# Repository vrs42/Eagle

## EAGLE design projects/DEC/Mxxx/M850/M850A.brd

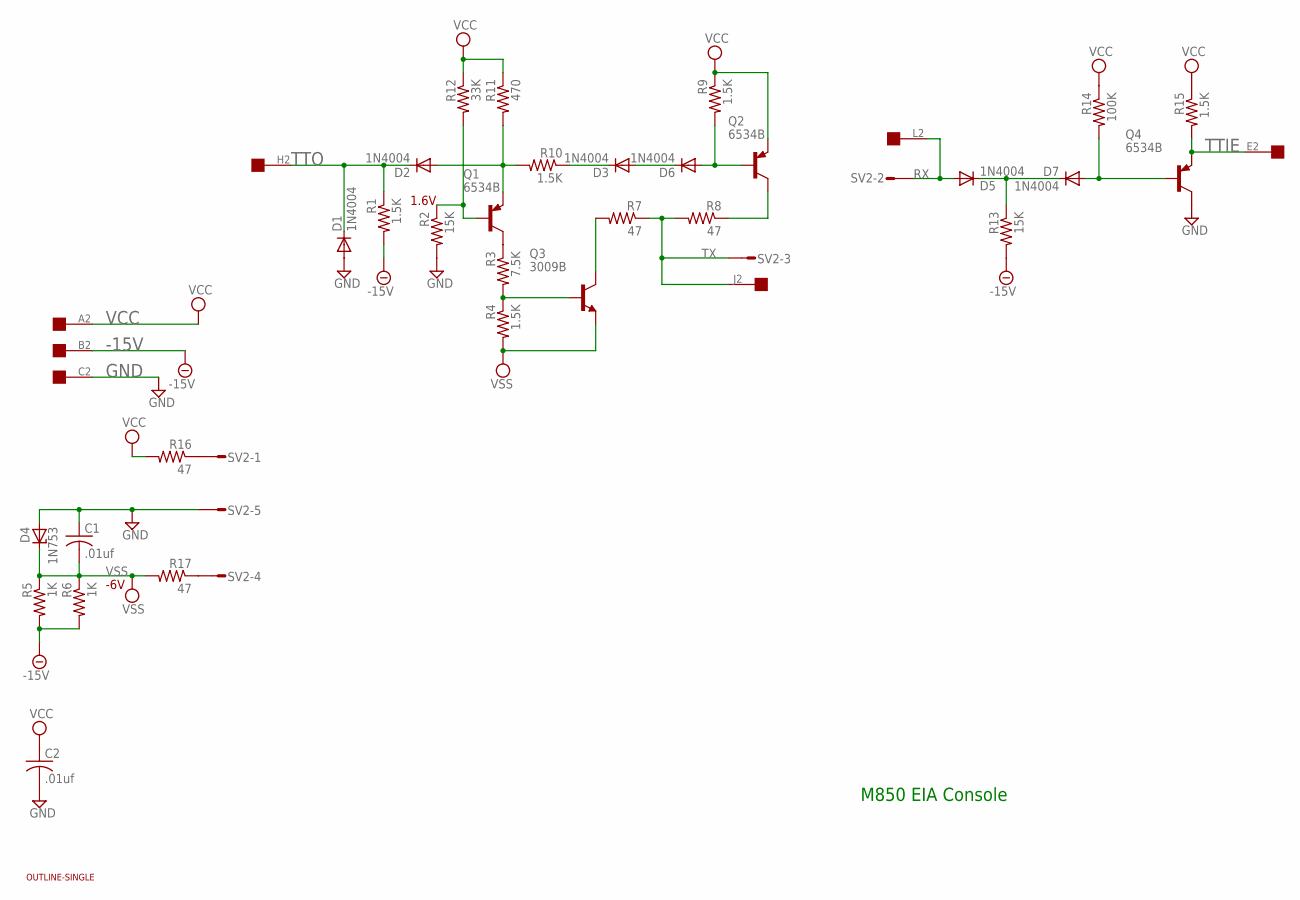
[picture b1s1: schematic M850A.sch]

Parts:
C1, C2: .01uf; C050-025X075
D1, D2, D3, D5, D6, D7: 1N4004; DO35-10
D4: 1N753; DO35Z10
EDGE: EDGE-1; EDGE-CON1
Q1, Q2, Q4: 6534B; TO92/
Q3: 3009B; TO18-
R1, R4, R9, R10, R15: 1.5K; 0207/10
R2, R13: 15K; 0207/10
R3: 7.5K; 0207/10
R5, R6: 1K; 0207/10
R7, R8, R16, R17: 47; 0207/10
R11: 470; 0207/10
R12: 33K; 0207/10
R14: 100K; 0207/10
SV2: L08P
U$1: OUTLINE-SINGLE; SINGLE

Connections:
-15V: EDGE.B2, R1.2, R5.2, R6.2, R13.2
GND: C1.1, C2.2, D1.A, D4.A, EDGE.C2, Q4.3 (C), R2.2, SV2.5
unnamed: Q2.3 (C), R8.1
unnamed: D7.A, Q4.2 (B), R14.2
unnamed: Q1.3 (C), R3.1
unnamed: R17.1, SV2.4
unnamed: Q3.3 (C), R7.2
unnamed: D5.C, D7.C, R13.1
unnamed: D2.A, Q1.1 (E), R10.2, R11.2
unnamed: D6.A, Q2.2 (B), R9.2
unnamed: Q1.2 (B), R2.1, R12.2
unnamed: D3.A, D6.C
unnamed: D3.C, R10.1
unnamed: Q3.2 (B), R3.2, R4.1
unnamed: R16.1, SV2.1
RX: D5.A, EDGE.L2, SV2.2
TTIE: EDGE.E2, Q4.1 (E), R15.2
TTO: D1.C, D2.C, EDGE.H2, R1.1
TX: EDGE.J2, R7.1, R8.2, SV2.3
VCC: C2.1, EDGE.A2, Q2.1 (E), R9.1, R11.1, R12.1, R14.1, R15.1, R16.2
VSS: C1.2, D4.C, Q3.1 (E), R4.2, R5.1, R6.1, R17.2

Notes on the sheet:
M850 EIA Console
1.6V
-6V

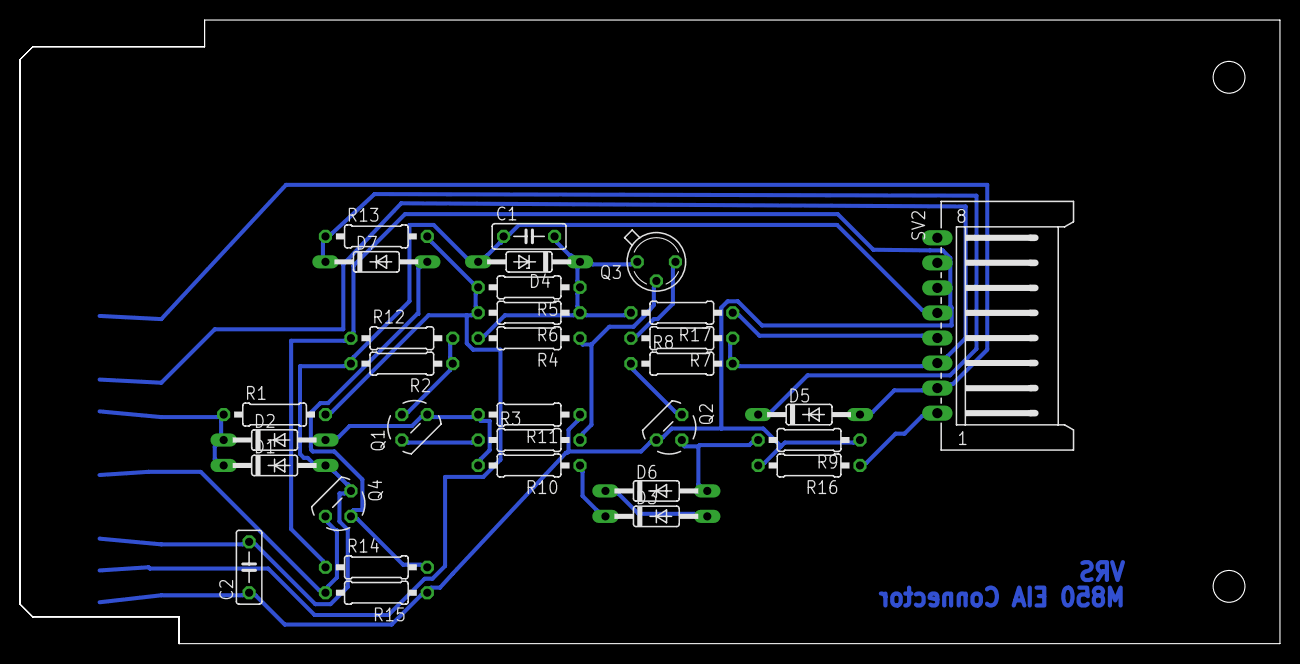
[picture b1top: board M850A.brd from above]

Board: 2 copper layers, 125.7 x 62.2 mm, 33 parts (0 on the bottom side), 21 nets.

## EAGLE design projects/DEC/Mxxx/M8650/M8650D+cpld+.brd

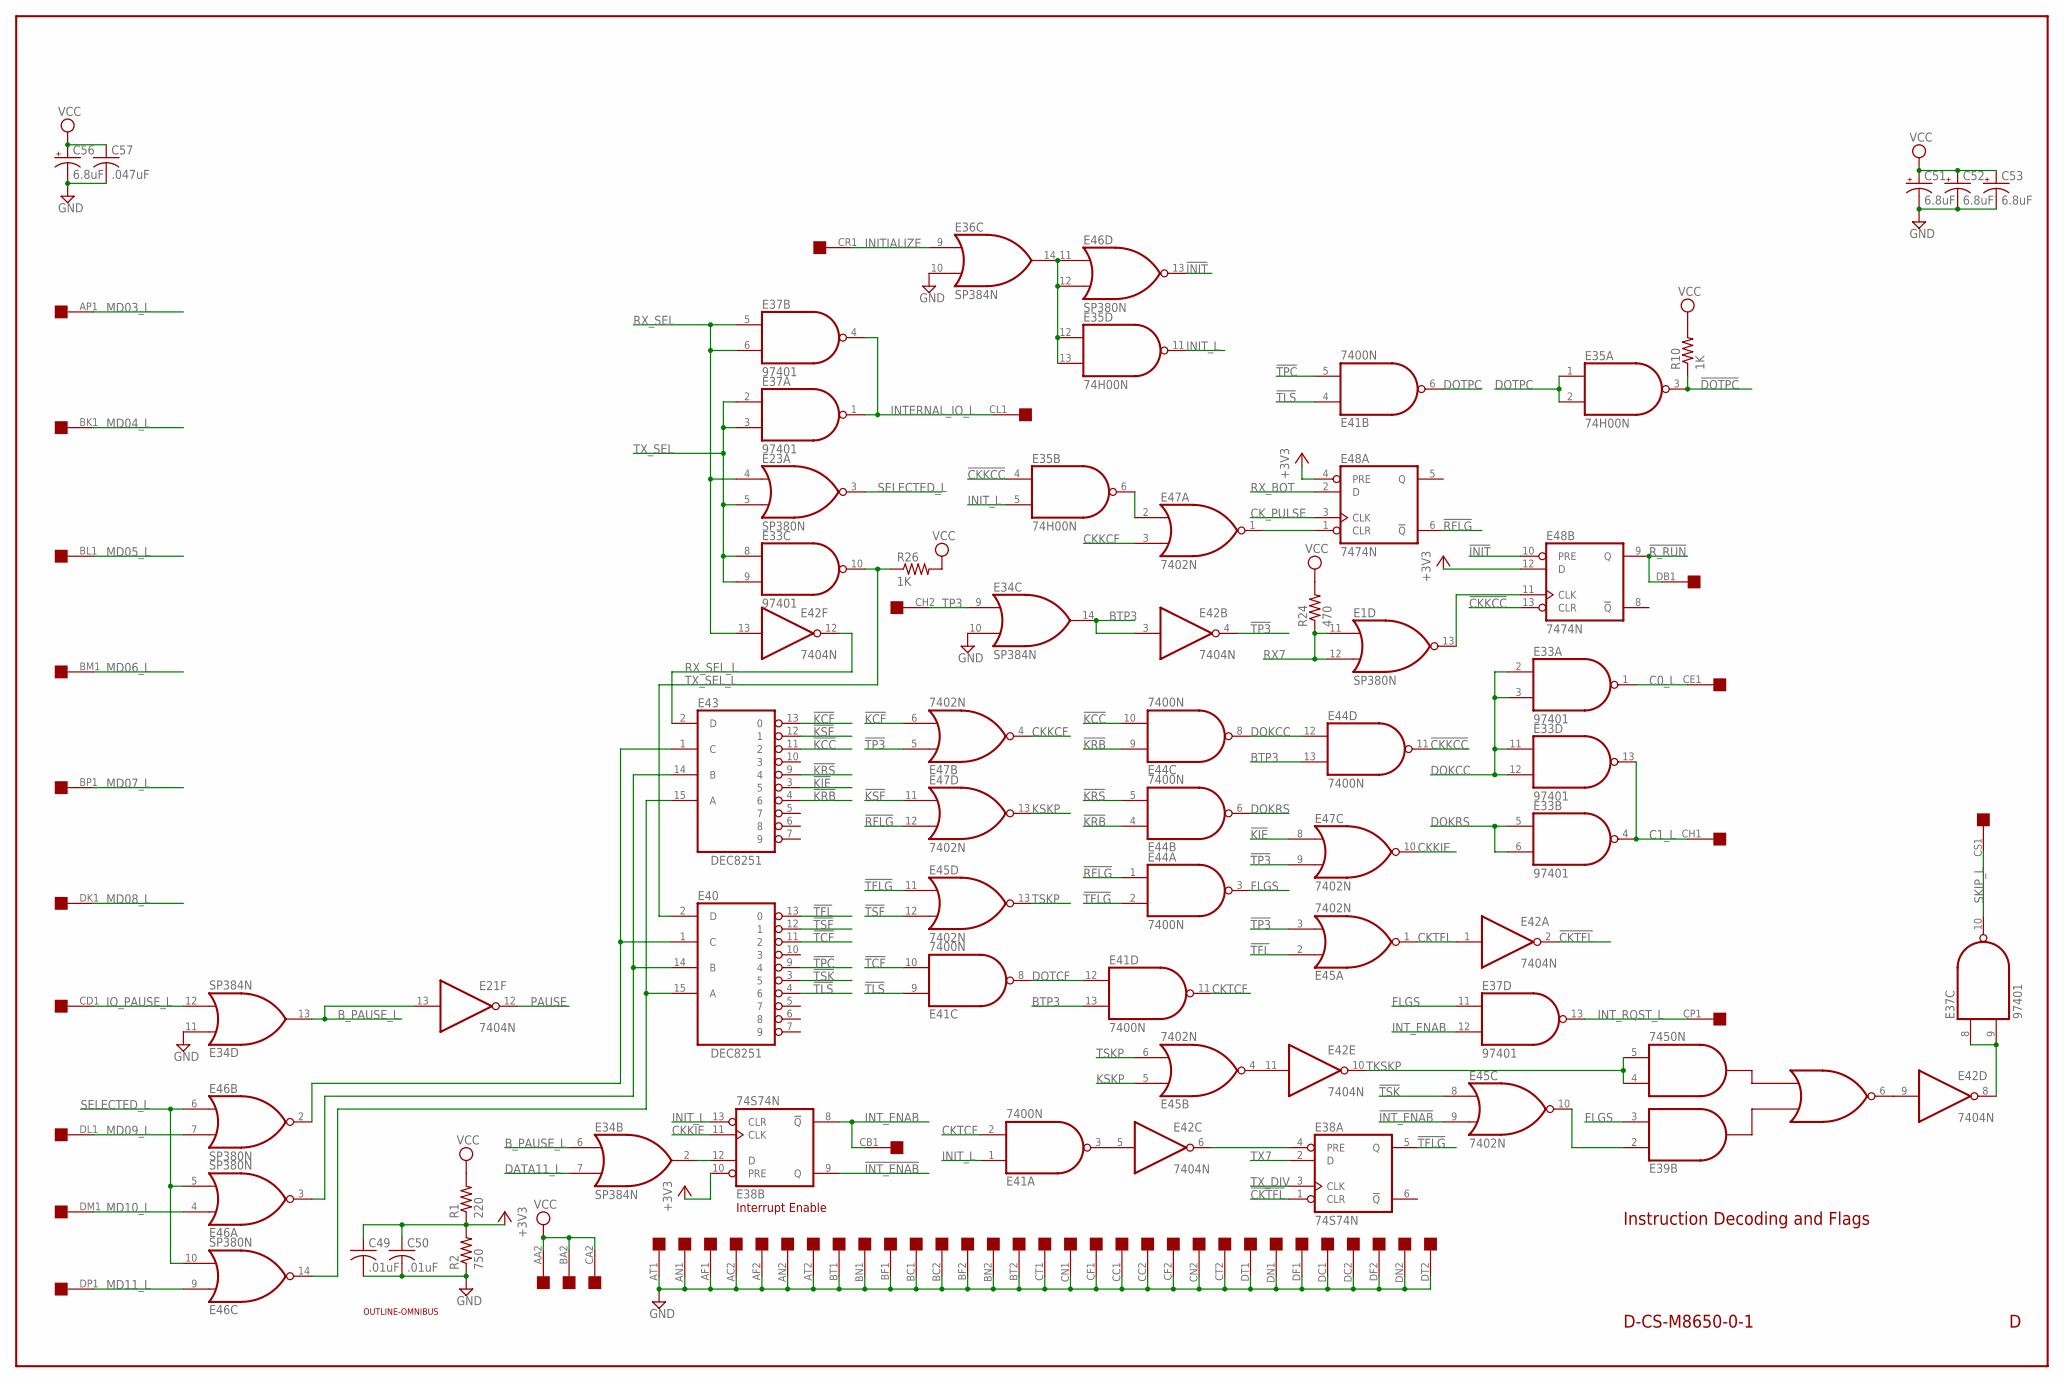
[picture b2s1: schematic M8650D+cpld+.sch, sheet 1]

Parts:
C49, C50: .01uF; C050-025X075
C51, C52, C53, C56: 6.8uF; E12-8
C57: .047uF; C050-025X075
E1, E23, E46: SP380N; DIL14
E21, E42: 7404N; DIL14
E33, E37: 97401; DIL14
E34, E36: SP384N; DIL14
E35: 74H00N; DIL14
E38: 74S74N; DIL14
E39: 7450N; DIL14
E40, E43: DEC8251; DIL16
E41, E44: 7400N; DIL14
E45, E47: 7402N; DIL14
E48: 7474N; DIL14
R1: 220; 0207/10
R2: 750; 0207/10
R10, R26: 1K; 0207/10
R24: 470; 0207/10
U$1: OUTLINE-OMNIBUS; OMNIBUS
U$2: OMNIBUS; EDGE-CON8

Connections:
!CKKCC: E35.4 (I0), E44.11 (O), E48.13 (CLR)
!CKTFL: E38.1 (CLR), E42.2 (O)
!DOTPC: E35.3 (O), R10.1; also elsewhere on the board
!INIT: E46.13 (O), E48.10 (PRE); also elsewhere on the board
!INT_ENAB: E38.9 (Q), E45.9 (I1)
!KCC: E43.11 (2), E44.10 (I1)
!KCF: E43.13 (0), E47.6 (I1)
!KIE: E43.3 (5), E47.8 (I0)
!KRB: E43.4 (6), E44.4 (I0), E44.9 (I0)
!KRS: E43.9 (4), E44.5 (I1)
!KSF: E43.12 (1), E47.11 (I0)
!RFLG: E44.1 (I0), E47.12 (I1), E48.6 (!Q)
!R_RUN: E48.9 (Q), U$2.DB1
!TCF: E40.11 (2), E41.10 (I1)
!TFL: E40.13 (0), E45.2 (I0)
!TFLG: E38.5 (Q), E44.2 (I1), E45.11 (I0)
!TLS: E40.4 (6), E41.4 (I0), E41.9 (I0)
!TP3: E42.4 (O), E45.3 (I1), E47.5 (I0), E47.9 (I1)
!TPC: E40.9 (4), E41.5 (I1)
!TSF: E40.12 (1), E45.12 (I1)
!TSK: E40.3 (5), E45.8 (I0)
+3V3: C49.1, C50.1, E38.10 (PRE), E48.4 (PRE), E48.12 (D), R1.1, R2.2; also elsewhere on the board
BTP3: E34.14 (O), E41.13 (I1), E42.3 (I), E44.13 (I1); also elsewhere on the board
B_PAUSE_L: E21.13 (I), E34.6 (I0), E34.13 (O)
C0_L: E33.1 (O), U$2.CE1
C1_L: E33.4 (O), E33.13 (O), U$2.CH1
CKKCF: E47.3 (I1), E47.4 (O)
CKKIE: E38.11 (CLK), E47.10 (O)
CKTCF: E41.2 (I1), E41.11 (O)
CKTFL: E42.1 (I), E45.1 (O)
CK_PULSE: E48.3 (CLK); also elsewhere on the board
DATA11_L: E34.7 (I1); also elsewhere on the board
DOKCC: E33.2 (I0), E33.3 (I1), E33.11 (I0), E33.12 (I1), E44.8 (O), E44.12 (I0)
DOKRS: E33.5 (I0), E33.6 (I1), E44.6 (O); also elsewhere on the board
DOTCF: E41.8 (O), E41.12 (I0)
DOTPC: E35.1 (I0), E35.2 (I1), E41.6 (O); also elsewhere on the board
FLGS: E37.11 (I0), E39.3 (I2), E44.3 (O)
GND: C49.2, C50.2, C51.-, C52.-, C53.-, C56.-, C57.2, E1.1 (GND), E21.7 (GND), E23.1 (GND), E33.7 (GND), E34.1 (GND), E34.10 (I1), E34.11 (I0), E35.7 (GND), E36.1 (GND), E36.10 (I1), E37.7 (GND), E38.7 (GND), E39.7 (GND), E40.8 (GND), E41.7 (GND), E42.7 (GND), E43.8 (GND), E44.7 (GND), E45.7 (GND), E46.1 (GND), E47.7 (GND), E48.7 (GND), R2.1, U$2.AC2, U$2.AF1, U$2.AF2, U$2.AN1, U$2.AN2, U$2.AT1, U$2.AT2, U$2.BC1, U$2.BC2, U$2.BF1, U$2.BF2, U$2.BN1, U$2.BN2, U$2.BT1, U$2.BT2, U$2.CC1, U$2.CC2, U$2.CF1, U$2.CF2, U$2.CN1, U$2.CN2, U$2.CT1, U$2.CT2, U$2.DC1, U$2.DC2, U$2.DF1, U$2.DF2, U$2.DN1, U$2.DN2, U$2.DT1, U$2.DT2; also elsewhere on the board
INITIALIZE: E36.9 (I0), U$2.CR1
INIT_L: E35.5 (I1), E35.11 (O), E38.13 (CLR), E41.1 (I0); also elsewhere on the board
INTERNAL_IO_L: E37.1 (O), E37.4 (O), U$2.CL1
INT_ENAB: E37.12 (I1), E38.8 (!Q), U$2.CB1
INT_RQST_L: E37.13 (O), U$2.CP1
IO_PAUSE_L: E34.12 (I1), U$2.CD1
KSKP: E45.5 (I0), E47.13 (O)
MD03_L: U$2.AP1; also elsewhere on the board
MD04_L: U$2.BK1; also elsewhere on the board
MD05_L: U$2.BL1; also elsewhere on the board
MD06_L: U$2.BM1; also elsewhere on the board
MD07_L: U$2.BP1; also elsewhere on the board
MD08_L: U$2.DK1; also elsewhere on the board
MD09_L: E46.7 (I1), U$2.DL1
MD10_L: E46.4 (I0), U$2.DM1
MD11_L: E46.9 (I0), U$2.DP1
unnamed: E34.2 (O), E38.12 (D)
unnamed: E42.11 (I), E45.4 (O)
unnamed: E35.12 (I0), E35.13 (I1), E36.14 (O), E46.11 (I0), E46.12 (I1)
unnamed: E41.3 (O), E42.5 (I)
unnamed: E38.4 (PRE), E42.6 (O)
unnamed: E39.2 (I1), E45.10 (O)
unnamed: E39.6 (O), E42.9 (I)
unnamed: E40.14 (B), E43.14 (B), E46.3 (O)
unnamed: E37.8 (I0), E37.9 (I1), E42.8 (O)
unnamed: E40.1 (C), E43.1 (C), E46.2 (O)
unnamed: E40.15 (A), E43.15 (A), E46.14 (O)
unnamed: E1.13 (O), E48.11 (CLK)
unnamed: E47.1 (O), E48.1 (CLR)
unnamed: E35.6 (O), E47.2 (I0)
PAUSE: E21.12 (O); also elsewhere on the board
RX7: E1.11 (I0), E1.12 (I1), R24.1; also elsewhere on the board
RX_BOT: E48.2 (D); also elsewhere on the board
RX_SEL: E23.4 (I0), E37.5 (I0), E37.6 (I1), E42.13 (I); also elsewhere on the board
RX_SEL_L: E42.12 (O), E43.2 (D)
SELECTED_L: E23.3 (O), E46.5 (I1), E46.6 (I0), E46.10 (I1)
SKIP_L: E37.10 (O), U$2.CS1
TKSKP: E39.4 (I3), E39.5 (I4), E42.10 (O)
TP3: E34.9 (I0), U$2.CH2; also elsewhere on the board
TSKP: E45.6 (I1), E45.13 (O)
TX7: E38.2 (D); also elsewhere on the board
TX_DIV: E38.3 (CLK); also elsewhere on the board
TX_SEL: E23.5 (I1), E33.8 (I0), E33.9 (I1), E37.2 (I0), E37.3 (I1); also elsewhere on the board
TX_SEL_L: E33.10 (O), E40.2 (D), R26.1
VCC: C51.+, C52.+, C53.+, C56.+, C57.1, E1.8 (VCC), E21.14 (VCC), E23.8 (VCC), E33.14 (VCC), E34.8 (VCC), E35.14 (VCC), E36.8 (VCC), E37.14 (VCC), E38.14 (VCC), E39.14 (VCC), E40.16 (VCC), E41.14 (VCC), E42.14 (VCC), E43.16 (VCC), E44.14 (VCC), E45.14 (VCC), E46.8 (VCC), E47.14 (VCC), E48.14 (VCC), R1.2, R10.2, R24.2, R26.2, U$2.AA2, U$2.BA2, U$2.CA2; also elsewhere on the board

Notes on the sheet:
Instruction Decoding and Flags
D-CS-M8650-0-1
Interrupt Enable

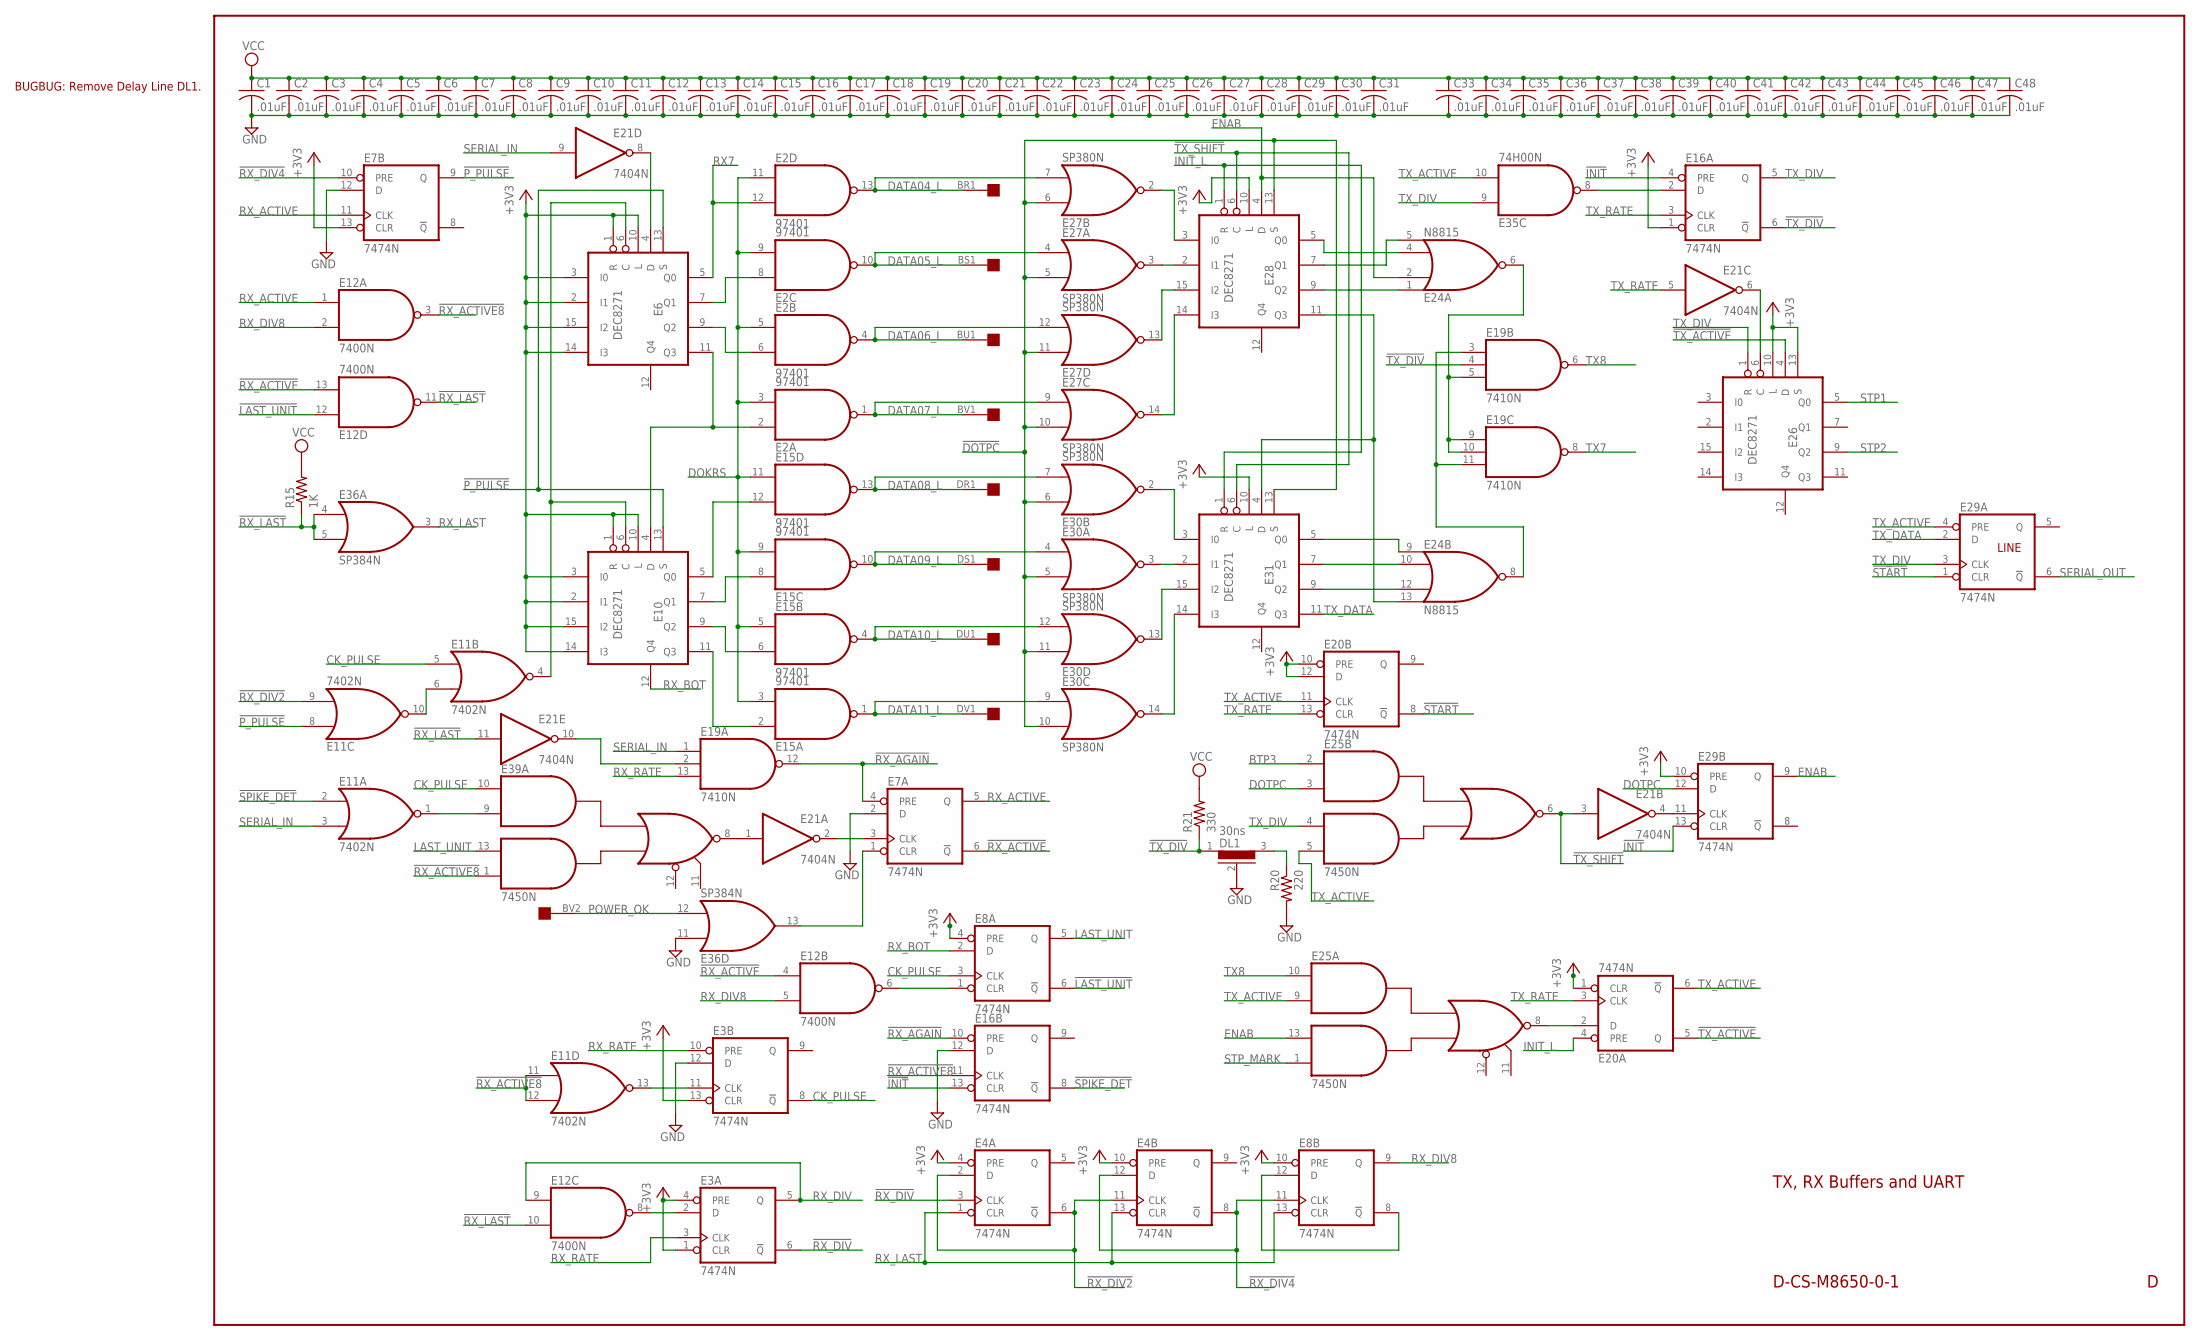
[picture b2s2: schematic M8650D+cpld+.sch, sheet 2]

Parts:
C1, C2, C3, C4, C5, C6, C7, C8, C9, C10, C11, C12, C13, C14, C15, C16, C17, C18, C19, C20, C21, C22, C23, C24, C25, C26, C27, C28, C29, C30, C31, C33, C34, C35, C36, C37, C38, C39, C40, C41, C42, C43, C44, C45, C46, C47, C48: .01uF; C050-025X075
DL1: 30ns; RCL-L-00-05
E2, E15: 97401; DIL14
E3, E4, E7, E8, E16, E20, E29: 7474N; DIL14
E6, E10, E26, E28, E31: DEC8271; DIL16
E11: 7402N; DIL14
E12: 7400N; DIL14
E19: 7410N; DIL14
E21: 7404N; DIL14
E24: N8815; DIL14
E25, E39: 7450N; DIL14
E27, E30: SP380N; DIL14
E35: 74H00N; DIL14
E36: SP384N; DIL14
R15: 1K; 0207/10
R20: 220; 0207/10
R21: 330; 0207/10
U$2: OMNIBUS; EDGE-CON8

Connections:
!DOTPC: E27.5 (I1), E27.6 (I0), E27.10 (I1), E27.11 (I0), E28.13 (S), E30.5 (I1), E30.6 (I0), E30.10 (I1), E30.11 (I0), E31.13 (S); also elsewhere on the board
!INIT: E16.4 (PRE), E16.13 (CLR), E29.13 (CLR); also elsewhere on the board
!LAST_UNIT: E8.6 (!Q), E12.12 (I0)
!P_PULSE: E6.13 (S), E7.9 (Q), E10.13 (S), E11.8 (I0)
!RX_ACTIVE: E7.6 (!Q), E12.4 (I0), E12.13 (I1)
!RX_ACTIVE8: E11.11 (I0), E11.12 (I1), E12.3 (O), E16.11 (CLK), E39.1 (I4)
!RX_AGAIN: E7.4 (PRE), E16.10 (PRE), E19.12 (O)
!RX_DIV: E3.6 (!Q), E4.3 (CLK)
!RX_DIV2: E4.2 (D), E4.6 (!Q), E4.11 (CLK), E11.9 (I1)
!RX_DIV4: E4.8 (!Q), E4.12 (D), E7.10 (PRE), E8.11 (CLK)
!RX_LAST: E12.10 (I1), E12.11 (O), E21.11 (I), E36.4 (I0), E36.5 (I1), R15.1
!SPIKE_DET: E11.2 (I0), E16.8 (!Q)
!START: E20.8 (!Q), E29.1 (CLR)
!TX_ACTIVE: E20.5 (Q), E26.4 (D)
!TX_DIV: DL1.1, E16.6 (!Q), E19.4 (I1), R21.1
!TX_SHIFT: E21.3 (I), E25.6 (O), E28.6 (C), E31.6 (C)
+3V3: E3.1 (CLR), E3.4 (PRE), E3.13 (CLR), E4.4 (PRE), E4.10 (PRE), E6.1 (R), E6.2 (I1), E6.3 (I0), E6.10 (L), E6.14 (I3), E6.15 (I2), E7.13 (CLR), E8.4 (PRE), E8.10 (PRE), E10.1 (R), E10.2 (I1), E10.3 (I0), E10.10 (L), E10.14 (I3), E10.15 (I2), E16.1 (CLR), E20.1 (CLR), E20.10 (PRE), E20.12 (D), E26.10 (L), E26.13 (S), E28.10 (L), E29.10 (PRE), E31.10 (L); also elsewhere on the board
BTP3: E25.2 (I1); also elsewhere on the board
CK_PULSE: E3.8 (!Q), E8.3 (CLK), E11.5 (I0), E39.10 (I1); also elsewhere on the board
DATA04_L: E2.13 (O), E27.7 (I1), U$2.BR1
DATA05_L: E2.10 (O), E27.4 (I0), U$2.BS1
DATA06_L: E2.4 (O), E27.12 (I1), U$2.BU1
DATA07_L: E2.1 (O), E27.9 (I0), U$2.BV1
DATA08_L: E15.13 (O), E30.7 (I1), U$2.DR1
DATA09_L: E15.10 (O), E30.4 (I0), U$2.DS1
DATA10_L: E15.4 (O), E30.12 (I1), U$2.DU1
DATA11_L: E15.1 (O), E30.9 (I0), U$2.DV1; also elsewhere on the board
DOKRS: E2.3 (I1), E2.5 (I0), E2.9 (I1), E2.11 (I0), E15.3 (I1), E15.5 (I0), E15.9 (I1), E15.11 (I0); also elsewhere on the board
DOTPC: E25.3 (I2), E29.12 (D); also elsewhere on the board
ENAB: E24.2 (I1), E25.13 (I3), E28.4 (D), E29.9 (Q)
GND: C1.2, C2.2, C3.2, C4.2, C5.2, C6.2, C7.2, C8.2, C9.2, C10.2, C11.2, C12.2, C13.2, C14.2, C15.2, C16.2, C17.2, C18.2, C19.2, C20.2, C21.2, C22.2, C23.2, C24.2, C25.2, C26.2, C27.2, C28.2, C29.2, C30.2, C31.2, C33.2, C34.2, C35.2, C36.2, C37.2, C38.2, C39.2, C40.2, C41.2, C42.2, C43.2, C44.2, C45.2, C46.2, C47.2, C48.2, DL1.2, E2.7 (GND), E3.7 (GND), E3.12 (D), E4.7 (GND), E6.8 (GND), E7.2 (D), E7.7 (GND), E7.12 (D), E8.7 (GND), E10.8 (GND), E11.7 (GND), E12.7 (GND), E15.7 (GND), E16.7 (GND), E16.12 (D), E19.7 (GND), E20.7 (GND), E21.7 (GND), E24.7 (GND), E25.7 (GND), E26.8 (GND), E27.1 (GND), E28.8 (GND), E29.7 (GND), E30.1 (GND), E31.8 (GND), E35.7 (GND), E36.1 (GND), E36.11 (I0), E39.7 (GND), R20.2; also elsewhere on the board
INIT_L: E20.4 (PRE), E28.1 (R), E31.1 (R); also elsewhere on the board
LAST_UNIT: E8.5 (Q), E39.13 (I3)
unnamed: E2.8 (I0), E6.7 (Q1)
unnamed: E2.2 (I0), E6.11 (Q3), E10.4 (D)
unnamed: E2.6 (I1), E6.9 (Q2)
unnamed: E10.5 (Q0), E15.12 (I1)
unnamed: E10.7 (Q1), E15.8 (I0)
unnamed: E10.9 (Q2), E15.6 (I1)
unnamed: E10.11 (Q3), E15.2 (I0)
unnamed: E6.6 (C), E10.6 (C), E11.4 (O)
unnamed: E11.6 (I1), E11.10 (O)
unnamed: E6.4 (D), E21.8 (O)
unnamed: E27.2 (O), E28.3 (I0)
unnamed: E27.3 (O), E28.2 (I1)
unnamed: E27.13 (O), E28.15 (I2)
unnamed: E27.14 (O), E28.14 (I3)
unnamed: E30.2 (O), E31.3 (I0)
unnamed: E30.3 (O), E31.2 (I1)
unnamed: E30.13 (O), E31.15 (I2)
unnamed: E30.14 (O), E31.14 (I3)
unnamed: E24.1 (I0), E28.9 (Q2)
unnamed: E24.4 (I2), E28.5 (Q0)
unnamed: E24.13 (I3), E28.11 (Q3), E31.4 (D)
unnamed: E24.5 (I3), E28.7 (Q1)
unnamed: E24.9 (I0), E31.5 (Q0)
unnamed: E24.10 (I1), E31.7 (Q1)
unnamed: E24.12 (I2), E31.9 (Q2)
unnamed: E7.3 (CLK), E21.2 (O)
unnamed: E19.3 (I0), E19.11 (I2), E24.8 (O)
unnamed: E19.5 (I2), E19.9 (I0), E19.10 (I1), E24.6 (O)
unnamed: E21.1 (I), E39.8 (O)
unnamed: E7.1 (CLR), E36.13 (O)
unnamed: E3.2 (D), E12.8 (O)
unnamed: E19.2 (I1), E21.10 (O)
unnamed: E11.1 (O), E39.9 (I2)
unnamed: E3.11 (CLK), E11.13 (O)
unnamed: E8.8 (!Q), E8.12 (D)
unnamed: E8.1 (CLR), E12.6 (O)
unnamed: E16.2 (D), E35.8 (O)
unnamed: E21.4 (O), E29.11 (CLK)
unnamed: DL1.3, R20.1
unnamed: E20.2 (D), E25.8 (O)
unnamed: E21.6 (O), E26.6 (C)
POWER_OK: E36.12 (I1), U$2.BV2
RX7: E2.12 (I1), E6.5 (Q0); also elsewhere on the board
RX_ACTIVE: E7.5 (Q), E7.11 (CLK), E12.1 (I0); also elsewhere on the board
RX_BOT: E8.2 (D), E10.12 (Q4); also elsewhere on the board
RX_DIV: E3.5 (Q), E12.9 (I0)
RX_DIV8: E8.9 (Q), E12.2 (I1), E12.5 (I1)
RX_LAST: E4.1 (CLR), E4.13 (CLR), E8.13 (CLR), E36.3 (O)
RX_RATE: E3.3 (CLK), E3.10 (PRE), E19.13 (I2); also elsewhere on the board
SERIAL_IN: E11.3 (I1), E19.1 (I0), E21.9 (I); also elsewhere on the board
SERIAL_OUT: E29.6 (!Q); also elsewhere on the board
STP1: E26.5 (Q0); also elsewhere on the board
STP2: E26.9 (Q2); also elsewhere on the board
STP_MARK: E25.1 (I4); also elsewhere on the board
TX7: E19.8 (O); also elsewhere on the board
TX8: E19.6 (O), E25.10 (I1)
TX_ACTIVE: E20.6 (!Q), E20.11 (CLK), E25.5 (I4), E25.9 (I2), E29.4 (PRE), E35.10 (I1); also elsewhere on the board
TX_DATA: E29.2 (D), E31.11 (Q3)
TX_DIV: E16.5 (Q), E25.4 (I3), E26.1 (R), E29.3 (CLK), E35.9 (I0); also elsewhere on the board
TX_RATE: E16.3 (CLK), E20.3 (CLK), E20.13 (CLR), E21.5 (I); also elsewhere on the board
VCC: C1.1, C2.1, C3.1, C4.1, C5.1, C6.1, C7.1, C8.1, C9.1, C10.1, C11.1, C12.1, C13.1, C14.1, C15.1, C16.1, C17.1, C18.1, C19.1, C20.1, C21.1, C22.1, C23.1, C24.1, C25.1, C26.1, C27.1, C28.1, C29.1, C30.1, C31.1, C33.1, C34.1, C35.1, C36.1, C37.1, C38.1, C39.1, C40.1, C41.1, C42.1, C43.1, C44.1, C45.1, C46.1, C47.1, C48.1, E2.14 (VCC), E3.14 (VCC), E4.14 (VCC), E6.16 (VCC), E7.14 (VCC), E8.14 (VCC), E10.16 (VCC), E11.14 (VCC), E12.14 (VCC), E15.14 (VCC), E16.14 (VCC), E19.14 (VCC), E20.14 (VCC), E21.14 (VCC), E24.14 (VCC), E25.14 (VCC), E26.16 (VCC), E27.8 (VCC), E28.16 (VCC), E29.14 (VCC), E30.8 (VCC), E31.16 (VCC), E35.14 (VCC), E36.8 (VCC), E39.14 (VCC), R15.2, R21.2; also elsewhere on the board

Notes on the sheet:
D-CS-M8650-0-1
TX, RX Buffers and UART
LINE
BUGBUG: Remove Delay Line DL1.

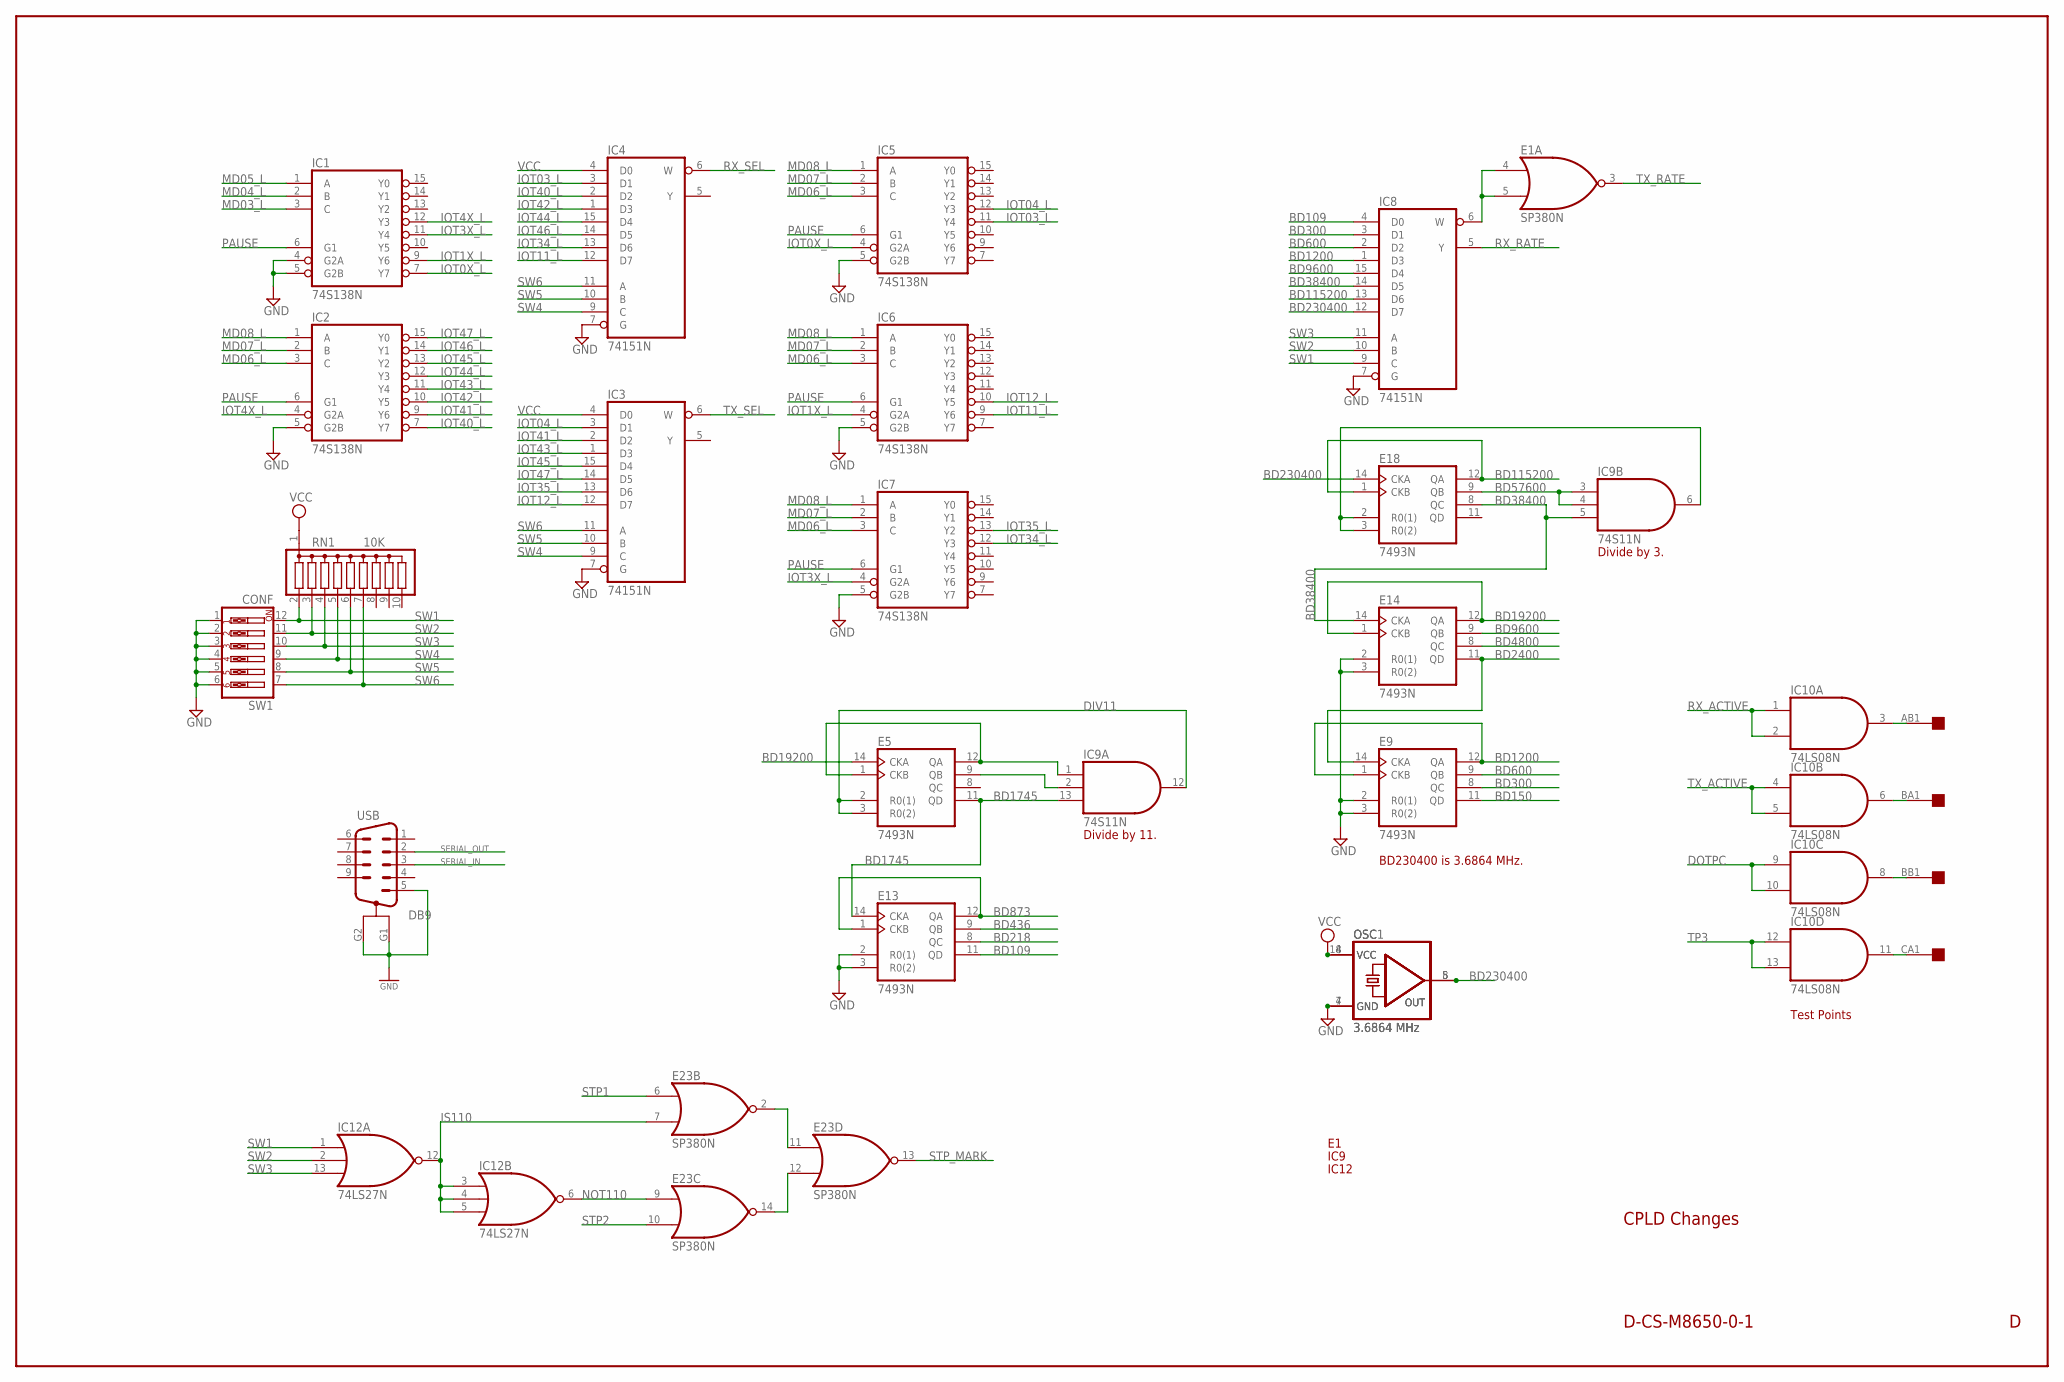
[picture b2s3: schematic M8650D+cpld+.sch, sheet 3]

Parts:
E1, E23: SP380N; DIL14
E5, E9, E13, E14, E18: 7493N; DIL14
IC1, IC2, IC5, IC6, IC7: 74S138N; DIL16
IC3, IC4, IC8: 74151N; DIL16
IC9: 74S11N; DIL14
IC10: 74LS08N; DIL14
IC12: 74LS27N; DIL14
OSC: 3.6864 MHz; DIL08S
OSC1: 3.6864 MHz; DIL14S
RN1: 10K; SIL10
SW1: CONF; EDG-06
U$2: OMNIBUS; EDGE-CON8
USB: DB9; AMP_DB-9RA

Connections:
BD109: E13.11 (QD), IC8.4 (D0)
BD150: E9.11 (QD)
BD218: E13.8 (QC)
BD300: E9.8 (QC), IC8.3 (D1)
BD436: E13.9 (QB)
BD600: E9.9 (QB), IC8.2 (D2)
BD873: E13.1 (CKB), E13.12 (QA)
BD1200: E9.1 (CKB), E9.12 (QA), IC8.1 (D3)
BD1745: E5.11 (QD), E13.14 (CKA), IC9.13 (I2)
BD2400: E9.14 (CKA), E14.11 (QD)
BD4800: E14.8 (QC)
BD9600: E14.9 (QB), IC8.15 (D4)
BD19200: E5.14 (CKA), E14.1 (CKB), E14.12 (QA)
BD38400: E14.14 (CKA), E18.8 (QC), IC8.14 (D5), IC9.5 (I2)
BD57600: E18.9 (QB), IC9.3 (I0), IC9.4 (I1)
BD115200: E18.1 (CKB), E18.12 (QA), IC8.13 (D6)
BD230400: E18.14 (CKA), IC8.12 (D7), OSC.5 (OUT), OSC1.8 (OUT)
DIV11: E5.2 (R0(1)), E5.3 (R0(2)), IC9.12 (O)
DOTPC: IC10.9 (I0), IC10.10 (I1); also elsewhere on the board
GND: E1.1 (GND), E5.10 (GND), E9.2 (R0(1)), E9.3 (R0(2)), E9.10 (GND), E13.2 (R0(1)), E13.3 (R0(2)), E13.10 (GND), E14.2 (R0(1)), E14.3 (R0(2)), E14.10 (GND), E18.10 (GND), E23.1 (GND), IC1.4 (G2A), IC1.5 (G2B), IC1.8 (GND), IC2.5 (G2B), IC2.8 (GND), IC3.7 (G), IC3.8 (GND), IC4.7 (G), IC4.8 (GND), IC5.5 (G2B), IC5.8 (GND), IC6.5 (G2B), IC6.8 (GND), IC7.5 (G2B), IC7.8 (GND), IC8.7 (G), IC8.8 (GND), IC9.7 (GND), IC10.7 (GND), IC12.7 (GND), OSC.4 (GND), OSC1.7 (GND), SW1.1, SW1.2, SW1.3, SW1.4, SW1.5, SW1.6, USB.5, USB.G1, USB.G2; also elsewhere on the board
IOT0X_L: IC1.7 (Y7), IC5.4 (G2A)
IOT1X_L: IC1.9 (Y6), IC6.4 (G2A)
IOT3X_L: IC1.11 (Y4), IC7.4 (G2A)
IOT03_L: IC4.3 (D1), IC5.11 (Y4)
IOT4X_L: IC1.12 (Y3), IC2.4 (G2A)
IOT04_L: IC3.3 (D1), IC5.12 (Y3)
IOT11_L: IC4.12 (D7), IC6.9 (Y6)
IOT12_L: IC3.12 (D7), IC6.10 (Y5)
IOT34_L: IC4.13 (D6), IC7.12 (Y3)
IOT35_L: IC3.13 (D6), IC7.13 (Y2)
IOT40_L: IC2.7 (Y7), IC4.2 (D2)
IOT41_L: IC2.9 (Y6), IC3.2 (D2)
IOT42_L: IC2.10 (Y5), IC4.1 (D3)
IOT43_L: IC2.11 (Y4), IC3.1 (D3)
IOT44_L: IC2.12 (Y3), IC4.15 (D4)
IOT45_L: IC2.13 (Y2), IC3.15 (D4)
IOT46_L: IC2.14 (Y1), IC4.14 (D5)
IOT47_L: IC2.15 (Y0), IC3.14 (D5)
IS110: E23.7 (I1), IC12.3 (I0), IC12.4 (I1), IC12.5 (I2), IC12.12 (O)
MD03_L: IC1.3 (C); also elsewhere on the board
MD04_L: IC1.2 (B); also elsewhere on the board
MD05_L: IC1.1 (A); also elsewhere on the board
MD06_L: IC2.3 (C), IC5.3 (C), IC6.3 (C), IC7.3 (C); also elsewhere on the board
MD07_L: IC2.2 (B), IC5.2 (B), IC6.2 (B), IC7.2 (B); also elsewhere on the board
MD08_L: IC2.1 (A), IC5.1 (A), IC6.1 (A), IC7.1 (A); also elsewhere on the board
unnamed: E1.4 (I0), E1.5 (I1), IC8.6 (W)
unnamed: E5.1 (CKB), E5.12 (QA), IC9.1 (I0)
unnamed: E18.2 (R0(1)), E18.3 (R0(2)), IC9.6 (O)
unnamed: E5.9 (QB), IC9.2 (I1)
unnamed: E23.12 (I1), E23.14 (O)
unnamed: E23.2 (O), E23.11 (I0)
NOT110: E23.9 (I0), IC12.6 (O)
PAUSE: IC1.6 (G1), IC2.6 (G1), IC5.6 (G1), IC6.6 (G1), IC7.6 (G1); also elsewhere on the board
RX_ACTIVE: IC10.1 (I0), IC10.2 (I1); also elsewhere on the board
RX_RATE: IC8.5 (Y); also elsewhere on the board
RX_SEL: IC4.6 (W); also elsewhere on the board
SERIAL_IN: USB.3; also elsewhere on the board
SERIAL_OUT: USB.2; also elsewhere on the board
STP1: E23.6 (I0); also elsewhere on the board
STP2: E23.10 (I1); also elsewhere on the board
STP_MARK: E23.13 (O); also elsewhere on the board
SW1: IC8.9 (C), IC12.1 (I0), RN1.2, SW1.12
SW2: IC8.10 (B), IC12.2 (I1), RN1.3, SW1.11
SW3: IC8.11 (A), IC12.13 (I2), RN1.4, SW1.10
SW4: IC3.9 (C), IC4.9 (C), RN1.5, SW1.9
SW5: IC3.10 (B), IC4.10 (B), RN1.6, SW1.8
SW6: IC3.11 (A), IC4.11 (A), RN1.7, SW1.7
TP3: IC10.12 (I0), IC10.13 (I1); also elsewhere on the board
TP_AB1: IC10.3 (O), U$2.AB1
TP_BA1: IC10.6 (O), U$2.BA1
TP_BB1: IC10.8 (O), U$2.BB1
TP_CA1: IC10.11 (O), U$2.CA1
TX_ACTIVE: IC10.4 (I0), IC10.5 (I1); also elsewhere on the board
TX_RATE: E1.3 (O); also elsewhere on the board
TX_SEL: IC3.6 (W); also elsewhere on the board
VCC: E1.8 (VCC), E5.5 (VCC), E9.5 (VCC), E13.5 (VCC), E14.5 (VCC), E18.5 (VCC), E23.8 (VCC), IC1.16 (VCC), IC2.16 (VCC), IC3.4 (D0), IC3.16 (VCC), IC4.4 (D0), IC4.16 (VCC), IC5.16 (VCC), IC6.16 (VCC), IC7.16 (VCC), IC8.16 (VCC), IC9.14 (VCC), IC10.14 (VCC), IC12.14 (VCC), OSC.8 (VCC), OSC1.14 (VCC), RN1.1; also elsewhere on the board

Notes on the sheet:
CPLD Changes
D-CS-M8650-0-1
BD230400 is 3.6864 MHz.
Divide by 11.
IC12
IC9
Divide by 3.
Test Points

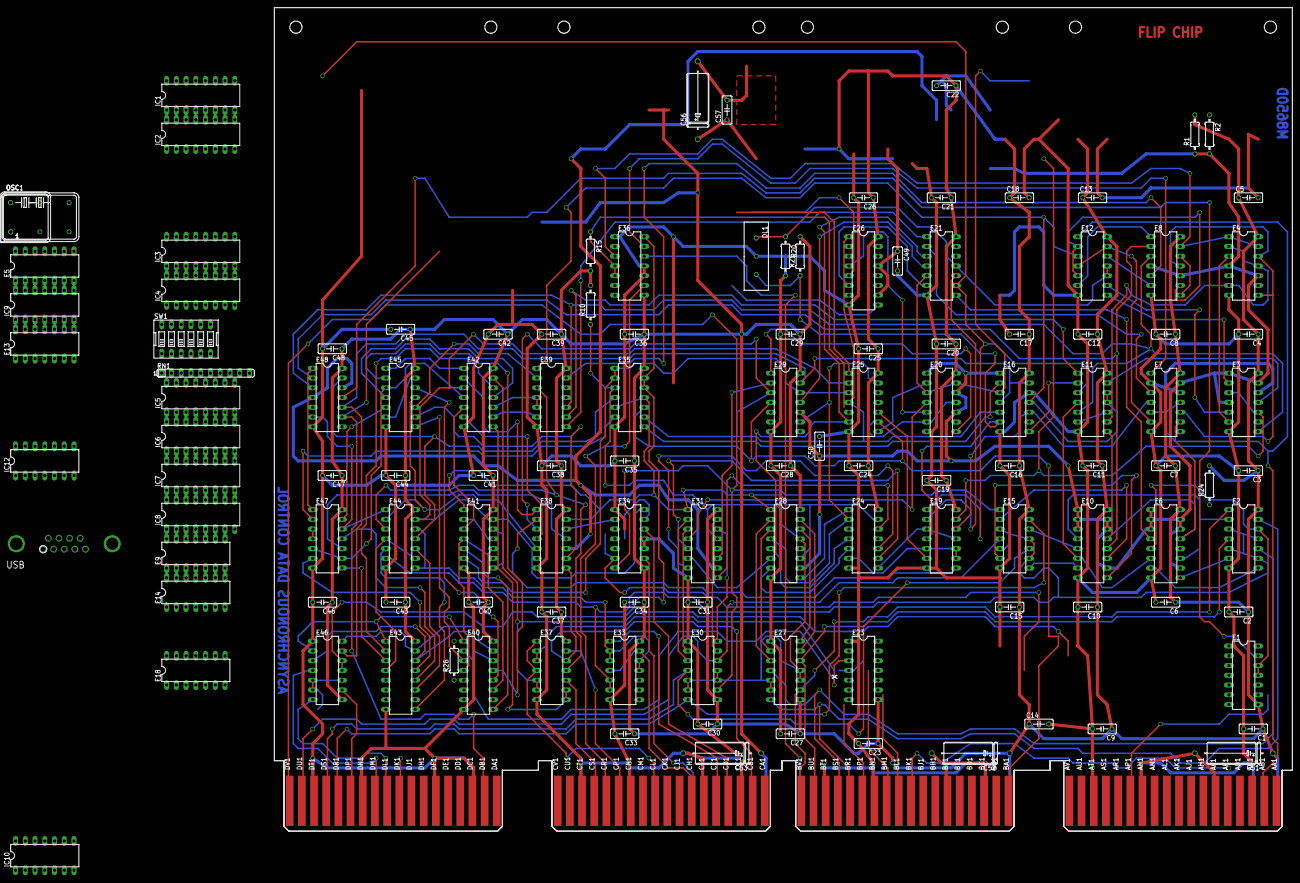
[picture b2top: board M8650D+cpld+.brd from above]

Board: 4 copper layers, 265.3 x 214.6 mm, 127 parts (0 on the bottom side), 212 nets.

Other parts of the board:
U$3: FLIPCHIP
